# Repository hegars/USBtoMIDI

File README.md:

# USBtoMIDI

KiCAD design for Isolated 1 IN, 1 THRU and 4 OUT (with disable) MIDI distributor with USB Host Midi controller based on Microchip 24FJ64GB002 microcontroller with code from (https://www.hobbytronics.co.uk/audio-midi/usb-host-midi) on a 100mm x 100mm board for low cost production

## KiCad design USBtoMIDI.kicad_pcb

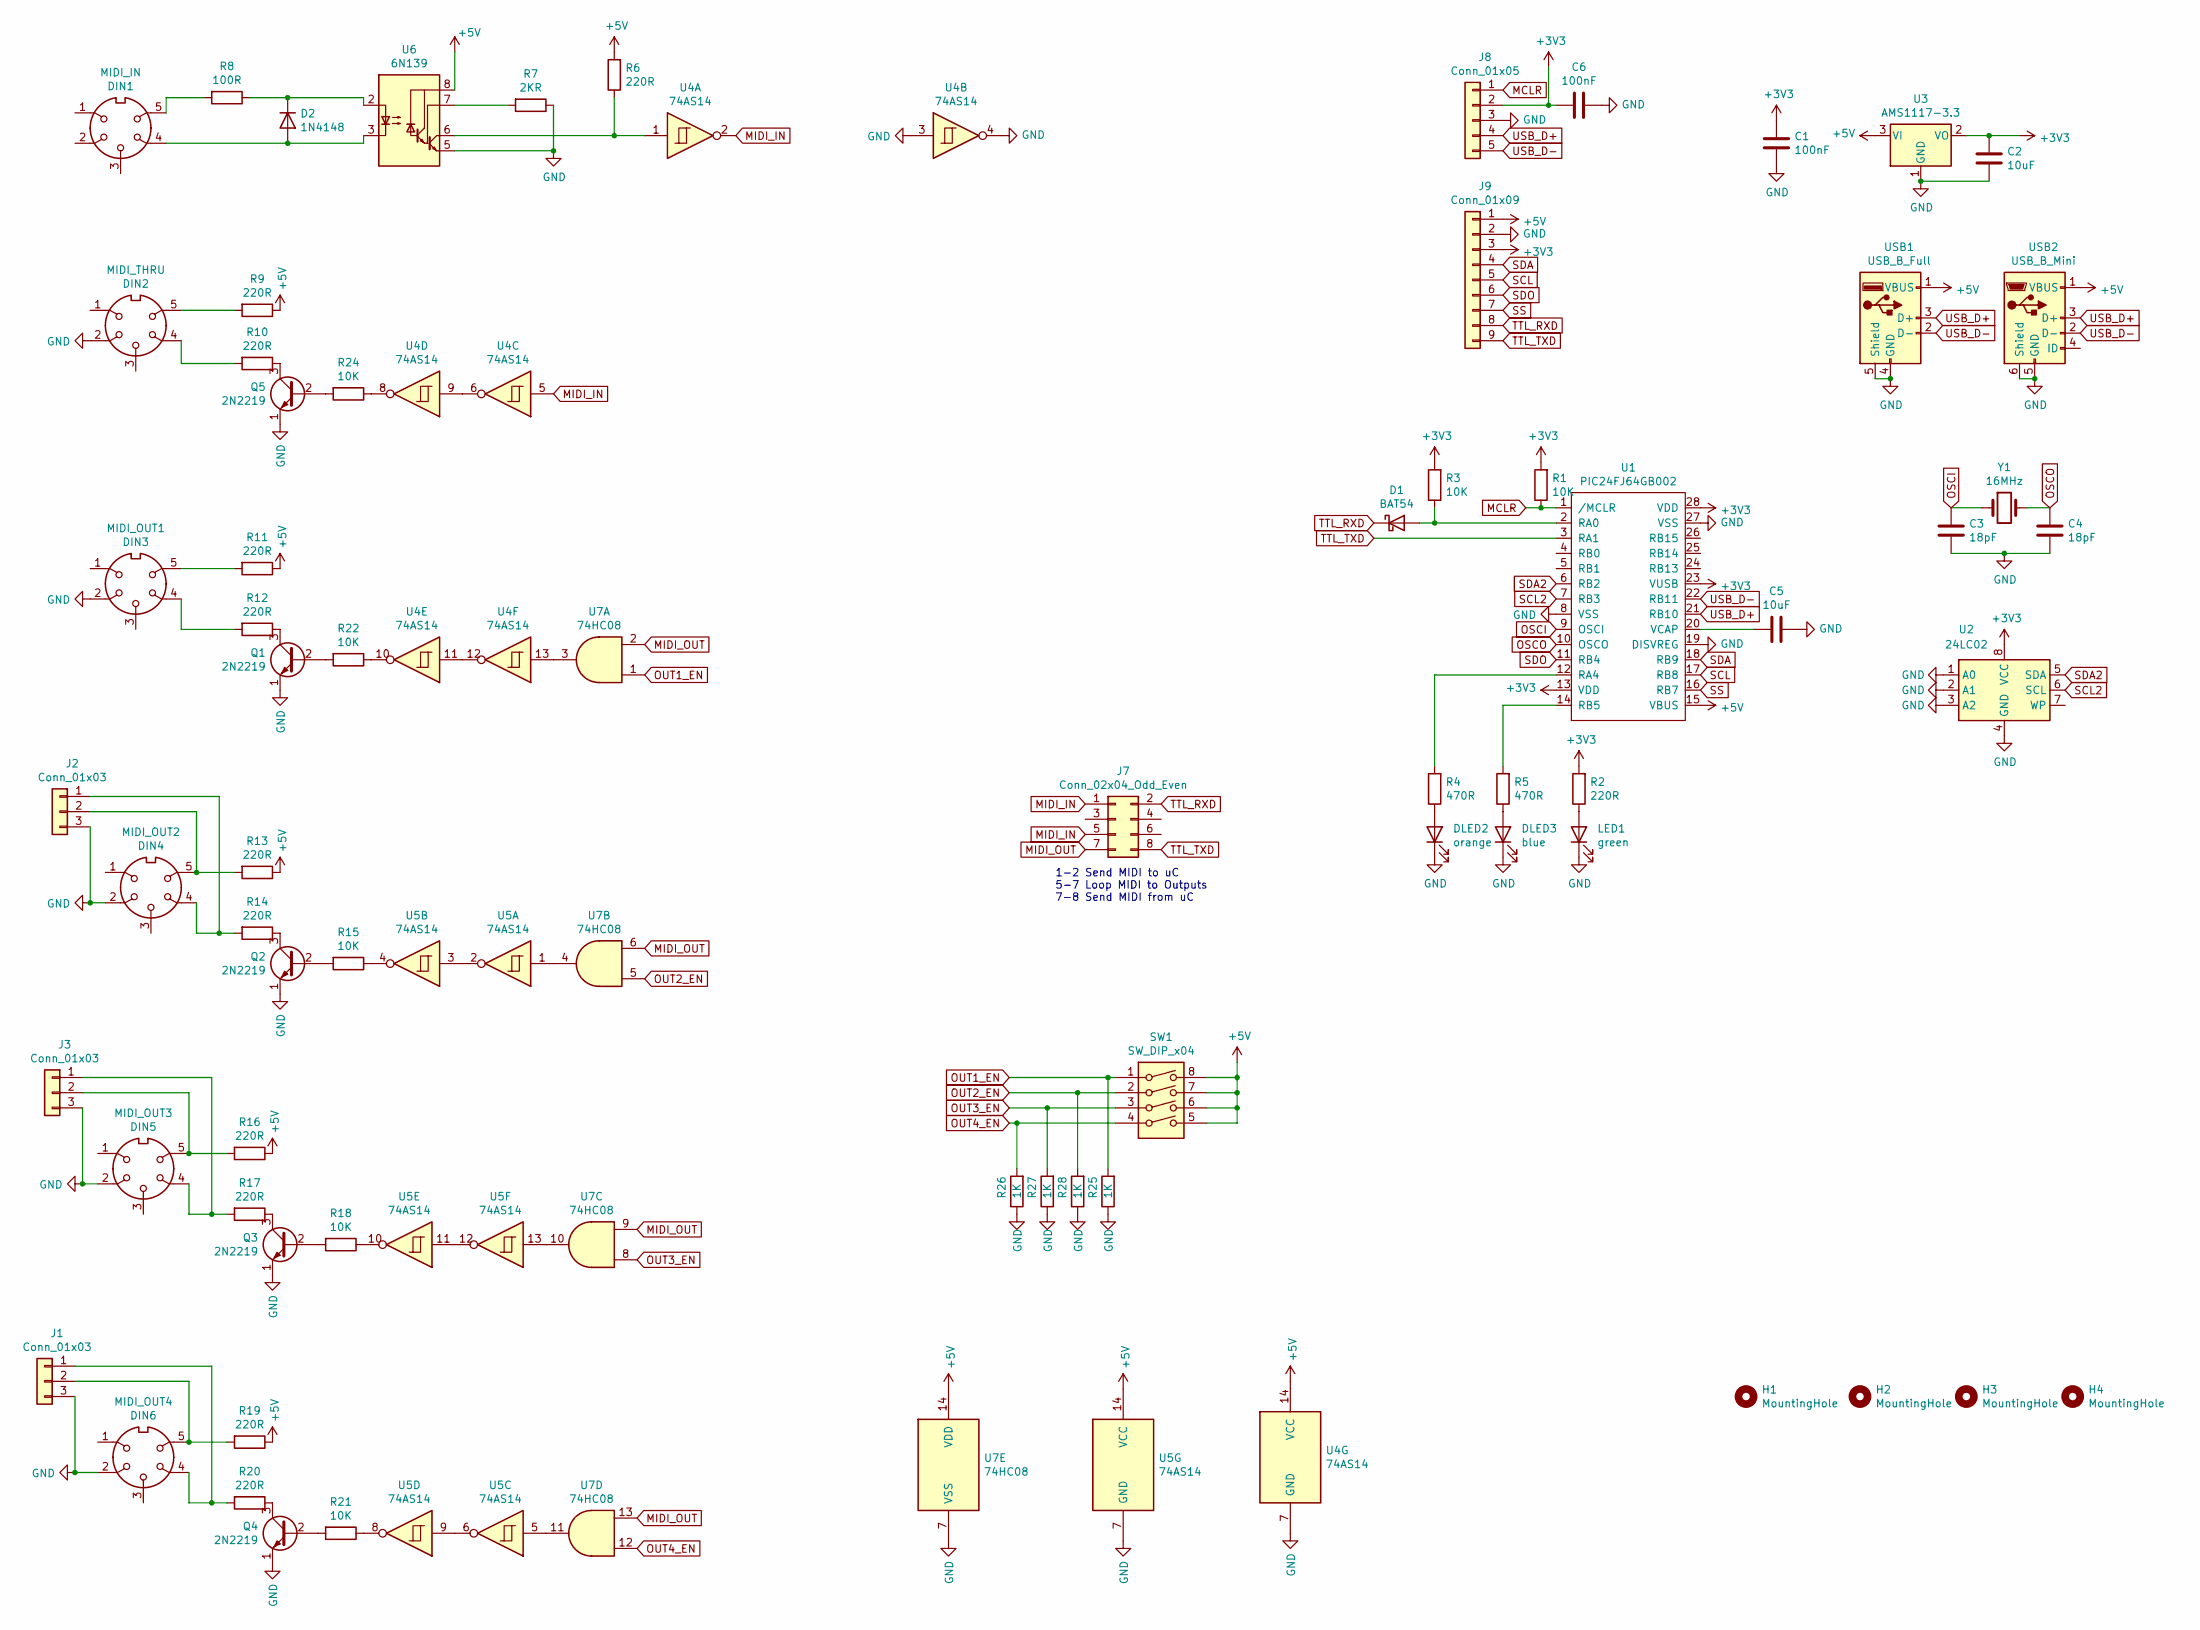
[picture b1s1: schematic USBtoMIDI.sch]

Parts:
C1, C6: 100nF; C_0805_HandSoldering
C2, C5: 10uF; C_0805_HandSoldering
C3, C4: 18pF; C_0805_HandSoldering
D1: BAT54; D_SOD-323
D2: 1N4148; D_1206
DIN1: MIDI_IN; din-5
DIN2: MIDI_THRU; din-5
DIN3: MIDI_OUT1; din-5
DIN4: MIDI_OUT2; din-5
DIN5: MIDI_OUT3; din-5
DIN6: MIDI_OUT4; din-5
DLED2: orange; LED_0805_HandSoldering
DLED3: blue; LED_0805_HandSoldering
H1, H2, H3, H4: MountingHole; MountingHole_3.2mm_M3_Pad_Via
J1, J2, J3: Conn_01x03; Pin_Header_Straight_1x03_Pitch2.54mm
J7: Conn_02x04_Odd_Even; Pin_Header_Straight_2x04_Pitch2.54mm
J8: Conn_01x05; Pin_Header_Straight_1x05_Pitch2.54mm
J9: Conn_01x09; Pin_Header_Straight_1x09_Pitch2.54mm
LED1: green; LED_0805_HandSoldering
Q1, Q2, Q3, Q4, Q5: 2N2219; SOT-23
R1, R3, R15, R18, R21, R22, R24: 10K; R_0805_HandSoldering
R2, R6, R9, R10, R11, R12, R13, R14, R16, R17, R19, R20: 220R; R_0805_HandSoldering
R4, R5: 470R; R_0805_HandSoldering
R7: 2KR; R_0805_HandSoldering
R8: 100R; R_0805_HandSoldering
R25, R26, R27, R28: 1K; R_0805_HandSoldering
SW1: SW_DIP_x04; SW_DIP_x4_W7.62mm_Slide
U1: PIC24FJ64GB002; SOIC-28
U2: 24LC02; SOIC-8_3.9x4.9mm_Pitch1.27mm
U3: AMS1117-3.3; SOT-223
U4, U5: 74AS14; SOIC-14_3.9x8.7mm_Pitch1.27mm
U6: 6N139; DIP-8_W7.62mm
U7: 74HC08; SOIC-14_3.9x8.7mm_Pitch1.27mm
USB1: USB_B_Full; USB_A_Vertical
USB2: USB_B_Mini; USB_Mini-B
Y1: 16MHz; Crystal_HC18-U_Vertical

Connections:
+3V3: C1.1, C2.1, C6.1, J8.2, J9.3, R1.2, R2.2, R3.2, U1.13 (VDD), U1.23 (VUSB), U1.28 (VDD), U2.8 (VCC), U3.2 (VO)
+5V: J9.1, R6.2, R9.1, R11.1, R13.1, R16.1, R19.1, SW1.5, SW1.6, SW1.7, SW1.8, U1.15 (VBUS), U3.3 (VI), U4.14 (VCC), U5.14 (VCC), U6.8 (VCC), U7.14 (VDD), USB1.1 (VBUS), USB2.1 (VBUS)
GND: C1.2, C2.2, C3.1, C4.1, C5.1, C6.2, DIN2.2, DIN3.2, DIN4.2, DIN5.2, DIN6.2, DLED2.1 (K), DLED3.1 (K), J1.3, J2.3, J3.3, J8.3, J9.2, LED1.1 (K), Q1.1 (E), Q2.1 (E), Q3.1 (E), Q4.1 (E), Q5.1 (E), R7.1, R25.1, R26.1, R27.1, R28.1, U1.8 (VSS), U1.19 (DISVREG), U1.27 (VSS), U2.1 (A0), U2.2 (A1), U2.3 (A2), U2.4 (GND), U3.1 (GND), U4.3, U4.4, U4.7 (GND), U5.7 (GND), U6.5 (GND), U7.7 (VSS), USB1.4 (GND), USB1.5 (Shield), USB2.5 (GND), USB2.6 (Shield)
MCLR: J8.1, R1.1, U1.1 (/MCLR)
MIDI_IN: J7.1, J7.5, U4.2, U4.5
MIDI_OUT: J7.7, U7.2, U7.6, U7.9, U7.13
unnamed: C5.2, U1.20 (VCAP)
unnamed: D1.2 (A), R3.1, U1.2 (RA0)
unnamed: D2.1 (K), R8.1, U6.2 (C1)
unnamed: D2.2 (A), DIN1.4, U6.3 (C2)
unnamed: DIN1.5, R8.2
unnamed: DIN2.4, R10.2
unnamed: DIN2.5, R9.2
unnamed: DIN3.4, R12.2
unnamed: DIN3.5, R11.2
unnamed: DIN4.4, J2.1, R14.2
unnamed: DIN4.5, J2.2, R13.2
unnamed: DIN5.4, J3.1, R17.2
unnamed: DIN5.5, J3.2, R16.2
unnamed: DIN6.4, J1.1, R20.2
unnamed: DIN6.5, J1.2, R19.2
unnamed: DLED2.2 (A), R4.1
unnamed: DLED3.2 (A), R5.1
unnamed: LED1.2 (A), R2.1
unnamed: Q1.2 (B), R22.2
unnamed: Q1.3 (C), R12.1
unnamed: Q2.2 (B), R15.2
unnamed: Q2.3 (C), R14.1
unnamed: Q3.2 (B), R18.2
unnamed: Q3.3 (C), R17.1
unnamed: Q4.2 (B), R21.2
unnamed: Q4.3 (C), R20.1
unnamed: Q5.2 (B), R24.2
unnamed: Q5.3 (C), R10.1
unnamed: R4.2, U1.12 (RA4)
unnamed: R5.2, U1.14 (RB5)
unnamed: R6.1, U4.1, U6.6 (VO2)
unnamed: R7.2, U6.7 (VO1)
unnamed: R15.1, U5.4
unnamed: R18.1, U5.10
unnamed: R21.1, U5.8
unnamed: R22.1, U4.10
unnamed: R24.1, U4.8
unnamed: U4.6, U4.9
unnamed: U4.11, U4.12
unnamed: U4.13, U7.3
unnamed: U5.1, U7.4
unnamed: U5.2, U5.3
unnamed: U5.5, U7.11
unnamed: U5.6, U5.9
unnamed: U5.11, U5.12
unnamed: U5.13, U7.10
OSCI: C3.2, U1.9 (OSCI), Y1.1
OSCO: C4.2, U1.10 (OSCO), Y1.2
OUT1_EN: R25.2, SW1.1, U7.1
OUT2_EN: R28.2, SW1.2, U7.5
OUT3_EN: R27.2, SW1.3, U7.8
OUT4_EN: R26.2, SW1.4, U7.12
SCL: J9.5, U1.17 (RB8)
SCL2: U1.7 (RB3), U2.6 (SCL)
SDA: J9.4, U1.18 (RB9)
SDA2: U1.6 (RB2), U2.5 (SDA)
SDO: J9.6, U1.11 (RB4)
SS: J9.7, U1.16 (RB7)
TTL_RXD: D1.1 (K), J7.2, J9.8
TTL_TXD: J7.8, J9.9, U1.3 (RA1)
USB_D+: J8.4, U1.21 (RB10), USB1.3 (D+), USB2.3 (D+)
USB_D-: J8.5, U1.22 (RB11), USB1.2 (D-), USB2.2 (D-)

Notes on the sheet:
1-2 Send MIDI to uC 5-7 Loop MIDI to Outputs 7-8 Send MIDI from uC

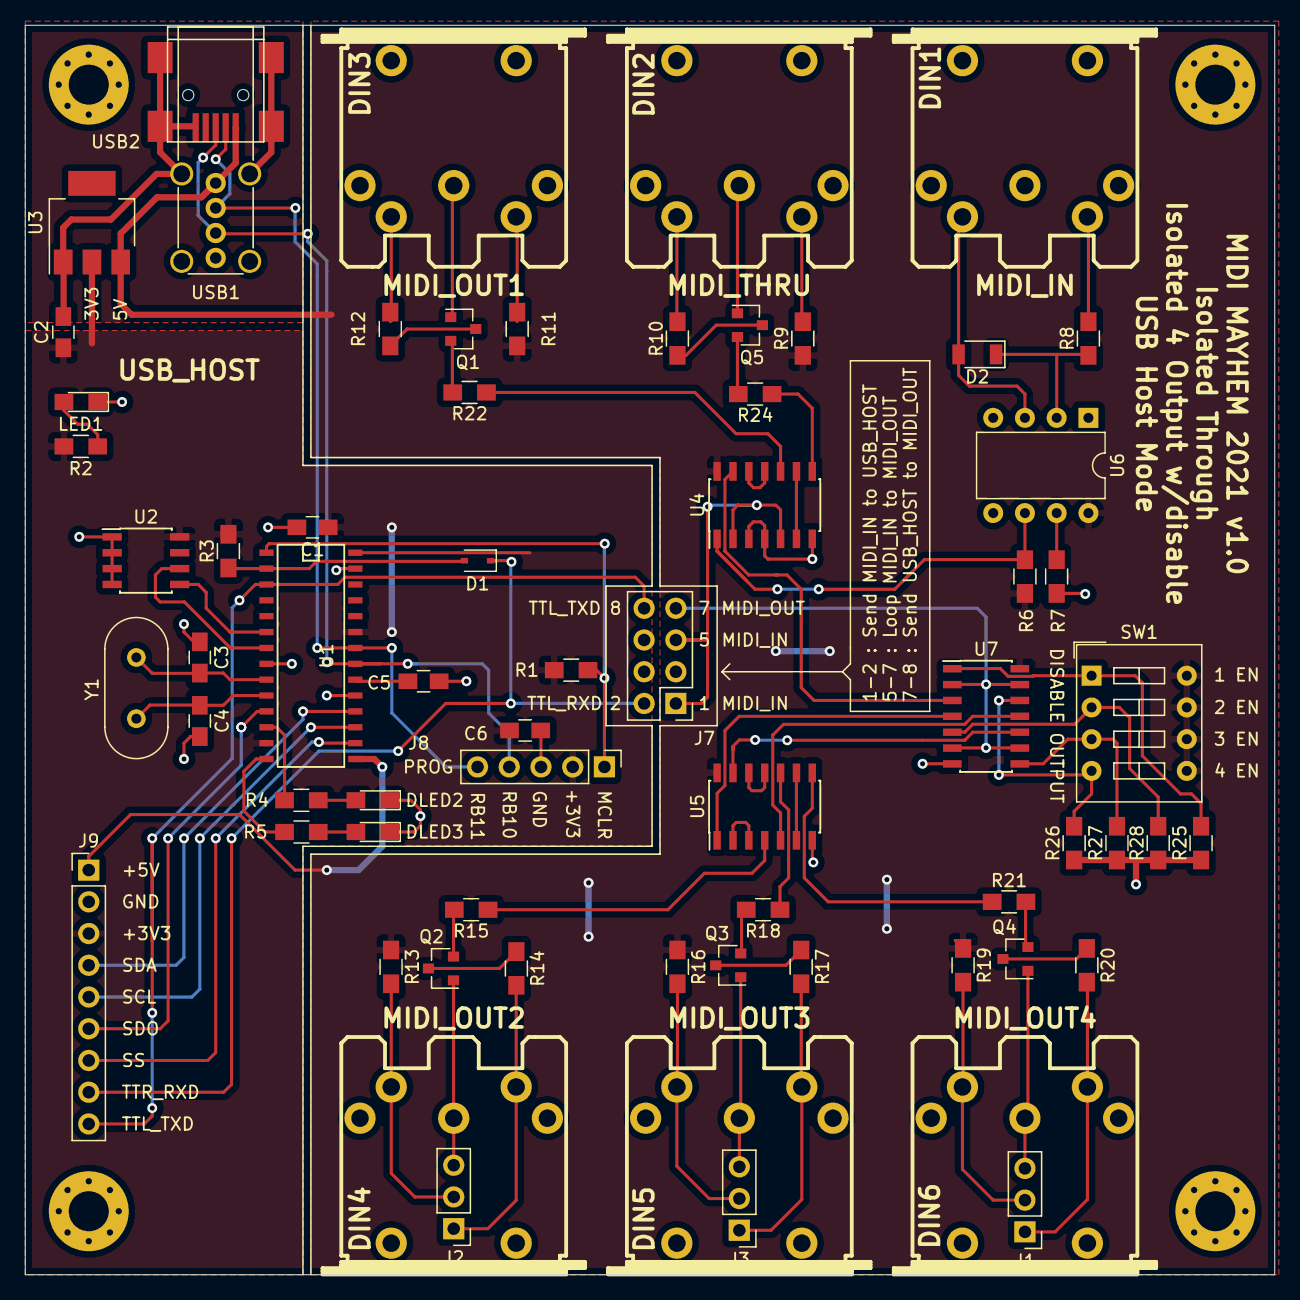
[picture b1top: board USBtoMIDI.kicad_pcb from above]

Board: 2 copper layers, 100.0 x 100.0 mm, 70 parts (0 on the bottom side), 68 nets.

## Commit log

2021-01-18 changed usb type
2021-01-18 update config ports
2021-01-18 update logic
2021-01-18 moving files around
2021-01-18 update sch pdf
2021-01-18 silk updates
2021-02-24 Update fp-info-cache
